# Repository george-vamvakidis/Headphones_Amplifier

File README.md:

# Headphones_Amplifier
Headphone amplifier design using NE5532 op-amp and Baxandall volume control. No pcb layout yet.

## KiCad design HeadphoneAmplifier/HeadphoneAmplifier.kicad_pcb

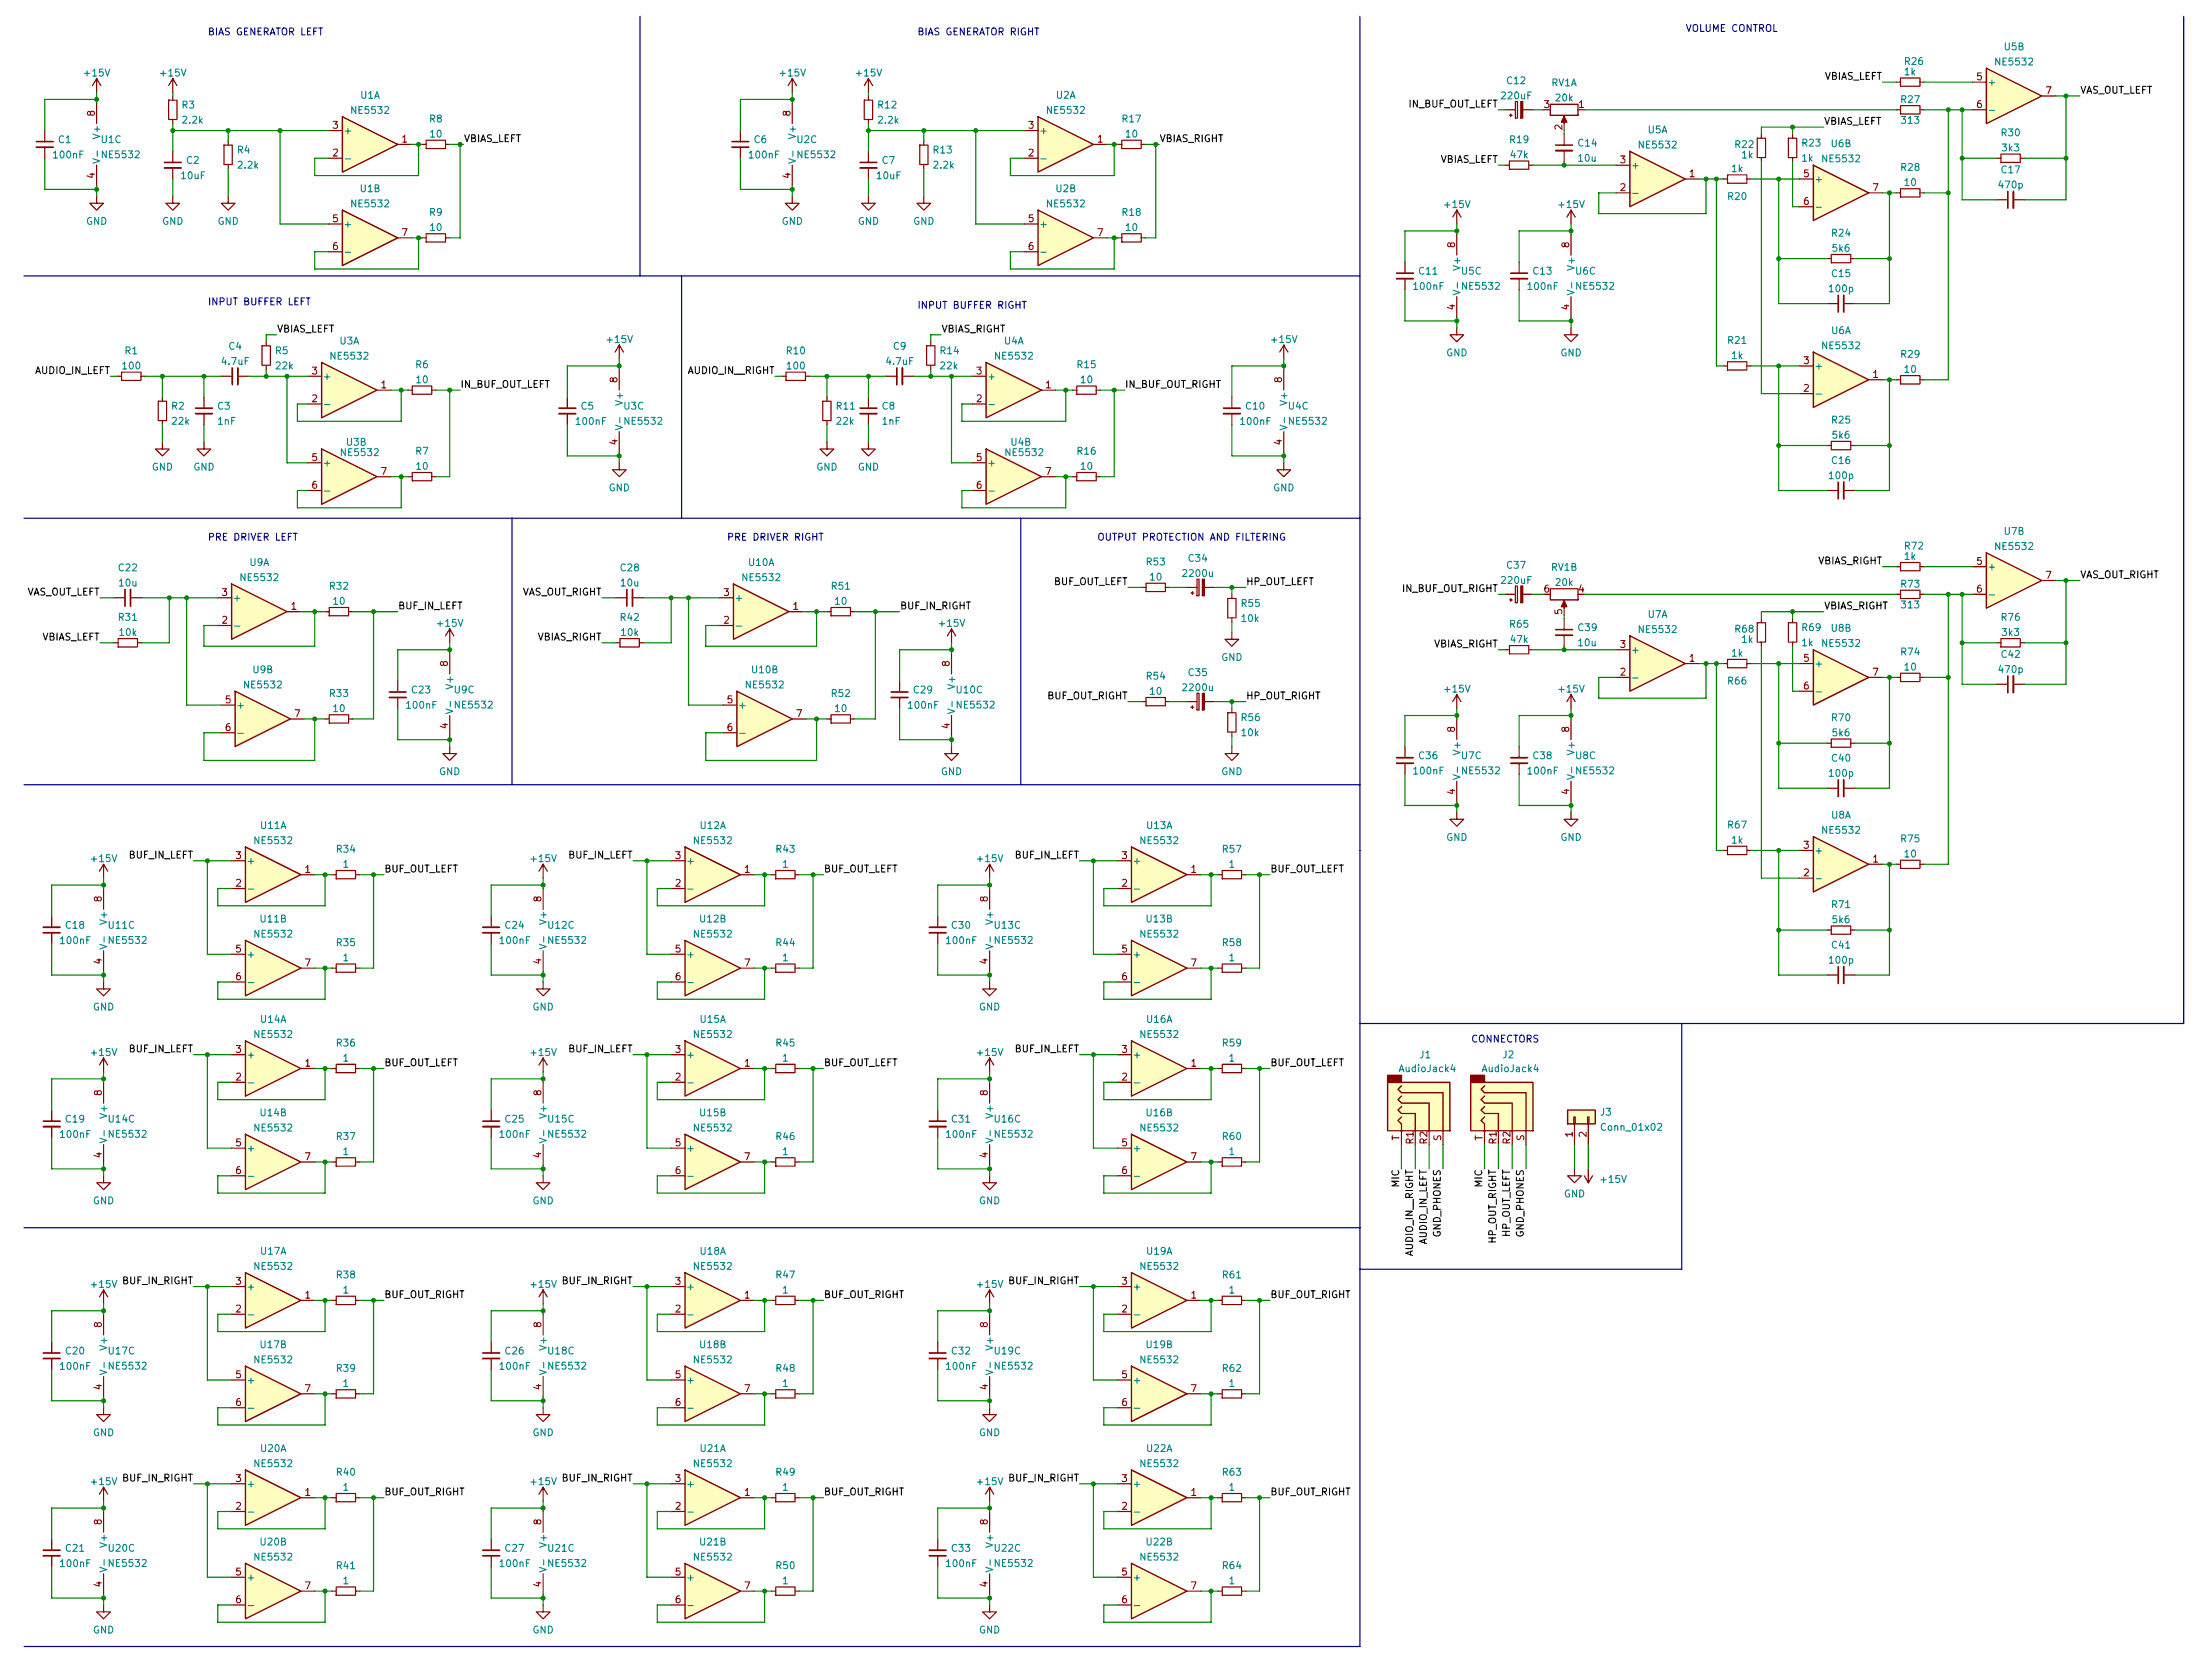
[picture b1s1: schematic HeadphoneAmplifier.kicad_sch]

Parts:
C1, C5, C6, C10, C11, C13, C18, C19, C20, C21, C23, C24, C25, C26, C27, C29, C30, C31, C32, C33, C36, C38: 100nF; C_0603_1608Metric
C2, C7: 10uF; C_0603_1608Metric
C3, C8: 1nF; C_0603_1608Metric
C4, C9: 4.7uF; C_0603_1608Metric
C12: 220uF; CP_Elec_4x5.4
C14, C22, C28, C39: 10u; C_0603_1608Metric
C15, C16, C40, C41: 100p; C_0603_1608Metric
C17, C42: 470p; C_0603_1608Metric
C34, C35: 2200u; CP_Radial_D16.0mm_P7.50mm
C37: 220uF; CP_Elec_10x10
J1, J2: AudioJack4; Jack_3.5mm_PJ320E_Horizontal
J3: Conn_01x02; TerminalBlock_Altech_AK300-2_P5.00mm
R1, R10: 100; R_1210_3225Metric
R2, R5, R11, R14: 22k; R_1210_3225Metric
R3, R4, R12, R13: 2.2k; R_1210_3225Metric
R6, R7, R8, R9, R15, R16, R17, R18, R28, R29, R32, R33, R51, R52, R53, R54, R74, R75: 10; R_1210_3225Metric
R19, R65: 47k; R_1210_3225Metric
R20, R21, R22, R23, R26, R66, R67, R68, R69, R72: 1k; R_1210_3225Metric
R24, R25, R70, R71: 5k6; R_1210_3225Metric
R27, R73: 313; R_1210_3225Metric
R30, R76: 3k3; R_1210_3225Metric
R31, R42, R55, R56: 10k; R_1210_3225Metric
R34, R35, R36, R37, R38, R39, R40, R41, R43, R44, R45, R46, R47, R48, R49, R50, R57, R58, R59, R60, R61, R62, R63, R64: 1; R_1210_3225Metric
RV1: 20k; Potentiometer_Piher_PC-16_Dual_Horizontal
U1, U2, U3, U4, U5, U6, U7, U8, U9, U10, U11, U12, U13, U14, U15, U16, U17, U18, U19, U20, U21, U22: NE5532; SOIC-8-1EP_3.9x4.9mm_P1.27mm_EP2.41x3.3mm

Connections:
+15V: C1.1, C5.1, C6.1, C10.1, C11.1, C13.1, C18.1, C19.1, C20.1, C21.1, C23.1, C24.1, C25.1, C26.1, C27.1, C29.1, C30.1, C31.1, C32.1, C33.1, C36.1, C38.1, J3.2, R3.1, R12.1, U1.8 (V+), U2.8 (V+), U3.8 (V+), U4.8 (V+), U5.8 (V+), U6.8 (V+), U7.8 (V+), U8.8 (V+), U9.8 (V+), U10.8 (V+), U11.8 (V+), U12.8 (V+), U13.8 (V+), U14.8 (V+), U15.8 (V+), U16.8 (V+), U17.8 (V+), U18.8 (V+), U19.8 (V+), U20.8 (V+), U21.8 (V+), U22.8 (V+)
/AUDIO_IN_LEFT: J1.R2, R1.1
/AUDIO_IN__RIGHT: J1.R1, R10.1
/BUF_IN_LEFT: R32.2, R33.2, U11.3 (+), U11.5 (+), U12.3 (+), U12.5 (+), U13.3 (+), U13.5 (+), U14.3 (+), U14.5 (+), U15.3 (+), U15.5 (+), U16.3 (+), U16.5 (+)
/BUF_IN_RIGHT: R51.2, R52.2, U17.3 (+), U17.5 (+), U18.3 (+), U18.5 (+), U19.3 (+), U19.5 (+), U20.3 (+), U20.5 (+), U21.3 (+), U21.5 (+), U22.3 (+), U22.5 (+)
/BUF_OUT_LEFT: R34.2, R35.2, R36.2, R37.2, R43.2, R44.2, R45.2, R46.2, R53.1, R57.2, R58.2, R59.2, R60.2
/BUF_OUT_RIGHT: R38.2, R39.2, R40.2, R41.2, R47.2, R48.2, R49.2, R50.2, R54.1, R61.2, R62.2, R63.2, R64.2
/GND_PHONES: J1.S, J2.S
/HP_OUT_LEFT: C34.2, J2.R2, R55.1
/HP_OUT_RIGHT: C35.2, J2.R1, R56.1
/IN_BUF_OUT_LEFT: C12.1, R6.2, R7.2
/IN_BUF_OUT_RIGHT: C37.1, R15.2, R16.2
/MIC: J1.T, J2.T
/VAS_OUT_LEFT: C17.2, C22.1, R30.2, U5.7
/VAS_OUT_RIGHT: C28.1, C42.2, R76.2, U7.7
/VBIAS_LEFT: R5.1, R8.2, R9.2, R19.1, R22.1, R23.1, R26.1, R31.1
/VBIAS_RIGHT: R14.1, R17.2, R18.2, R42.1, R65.1, R68.1, R69.1, R72.1
GND: C1.2, C2.2, C3.2, C5.2, C6.2, C7.2, C8.2, C10.2, C11.2, C13.2, C18.2, C19.2, C20.2, C21.2, C23.2, C24.2, C25.2, C26.2, C27.2, C29.2, C30.2, C31.2, C32.2, C33.2, C36.2, C38.2, J3.1, R2.2, R4.2, R11.2, R13.2, R55.2, R56.2, U1.4 (V-), U2.4 (V-), U3.4 (V-), U4.4 (V-), U5.4 (V-), U6.4 (V-), U7.4 (V-), U8.4 (V-), U9.4 (V-), U10.4 (V-), U11.4 (V-), U12.4 (V-), U13.4 (V-), U14.4 (V-), U15.4 (V-), U16.4 (V-), U17.4 (V-), U18.4 (V-), U19.4 (V-), U20.4 (V-), U21.4 (V-), U22.4 (V-)
unnamed: C2.1, R3.2, R4.1, U1.3 (+), U1.5 (+)
unnamed: C3.1, C4.1, R1.2, R2.1
unnamed: C4.2, R5.2, U3.3 (+), U3.5 (+)
unnamed: C7.1, R12.2, R13.1, U2.3 (+), U2.5 (+)
unnamed: C8.1, C9.1, R10.2, R11.1
unnamed: C9.2, R14.2, U4.3 (+), U4.5 (+)
unnamed: C12.2, RV1.3
unnamed: C14.1, RV1.2
unnamed: C14.2, R19.2, U5.3 (+)
unnamed: C15.1, R20.2, R24.1, U6.5 (+)
unnamed: C15.2, R24.2, R28.1, U6.7
unnamed: C16.1, R21.2, R25.1, U6.3 (+)
unnamed: C16.2, R25.2, R29.1, U6.1
unnamed: C17.1, R27.2, R28.2, R29.2, R30.1, U5.6 (-)
unnamed: C22.2, R31.2, U9.3 (+), U9.5 (+)
unnamed: C28.2, R42.2, U10.3 (+), U10.5 (+)
unnamed: C34.1, R53.2
unnamed: C35.1, R54.2
unnamed: C37.2, RV1.6
unnamed: C39.1, RV1.5
unnamed: C39.2, R65.2, U7.3 (+)
unnamed: C40.1, R66.2, R70.1, U8.5 (+)
unnamed: C40.2, R70.2, R74.1, U8.7
unnamed: C41.1, R67.2, R71.1, U8.3 (+)
unnamed: C41.2, R71.2, R75.1, U8.1
unnamed: C42.1, R73.2, R74.2, R75.2, R76.1, U7.6 (-)
unnamed: R6.1, U3.1, U3.2 (-)
unnamed: R7.1, U3.6 (-), U3.7
unnamed: R8.1, U1.1, U1.2 (-)
unnamed: R9.1, U1.6 (-), U1.7
unnamed: R15.1, U4.1, U4.2 (-)
unnamed: R16.1, U4.6 (-), U4.7
unnamed: R17.1, U2.1, U2.2 (-)
unnamed: R18.1, U2.6 (-), U2.7
unnamed: R20.1, R21.1, U5.1, U5.2 (-)
unnamed: R22.2, U6.2 (-)
unnamed: R23.2, U6.6 (-)
unnamed: R26.2, U5.5 (+)
unnamed: R27.1, RV1.1
unnamed: R32.1, U9.1, U9.2 (-)
unnamed: R33.1, U9.6 (-), U9.7
unnamed: R34.1, U11.1, U11.2 (-)
unnamed: R35.1, U11.6 (-), U11.7
unnamed: R36.1, U14.1, U14.2 (-)
unnamed: R37.1, U14.6 (-), U14.7
unnamed: R38.1, U17.1, U17.2 (-)
unnamed: R39.1, U17.6 (-), U17.7
unnamed: R40.1, U20.1, U20.2 (-)
unnamed: R41.1, U20.6 (-), U20.7
unnamed: R43.1, U12.1, U12.2 (-)
unnamed: R44.1, U12.6 (-), U12.7
unnamed: R45.1, U15.1, U15.2 (-)
unnamed: R46.1, U15.6 (-), U15.7
unnamed: R47.1, U18.1, U18.2 (-)
unnamed: R48.1, U18.6 (-), U18.7
unnamed: R49.1, U21.1, U21.2 (-)
unnamed: R50.1, U21.6 (-), U21.7
unnamed: R51.1, U10.1, U10.2 (-)
unnamed: R52.1, U10.6 (-), U10.7
unnamed: R57.1, U13.1, U13.2 (-)
unnamed: R58.1, U13.6 (-), U13.7
unnamed: R59.1, U16.1, U16.2 (-)
unnamed: R60.1, U16.6 (-), U16.7
unnamed: R61.1, U19.1, U19.2 (-)
unnamed: R62.1, U19.6 (-), U19.7
unnamed: R63.1, U22.1, U22.2 (-)
unnamed: R64.1, U22.6 (-), U22.7
unnamed: R66.1, R67.1, U7.1, U7.2 (-)
unnamed: R68.2, U8.2 (-)
unnamed: R69.2, U8.6 (-)
unnamed: R72.2, U7.5 (+)
unnamed: R73.1, RV1.4

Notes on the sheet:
PRE DRIVER RIGHT
PRE DRIVER LEFT
INPUT BUFFER LEFT
VOLUME CONTROL
OUTPUT PROTECTION AND FILTERING
CONNECTORS
INPUT BUFFER RIGHT
BIAS GENERATOR RIGHT
BIAS GENERATOR LEFT

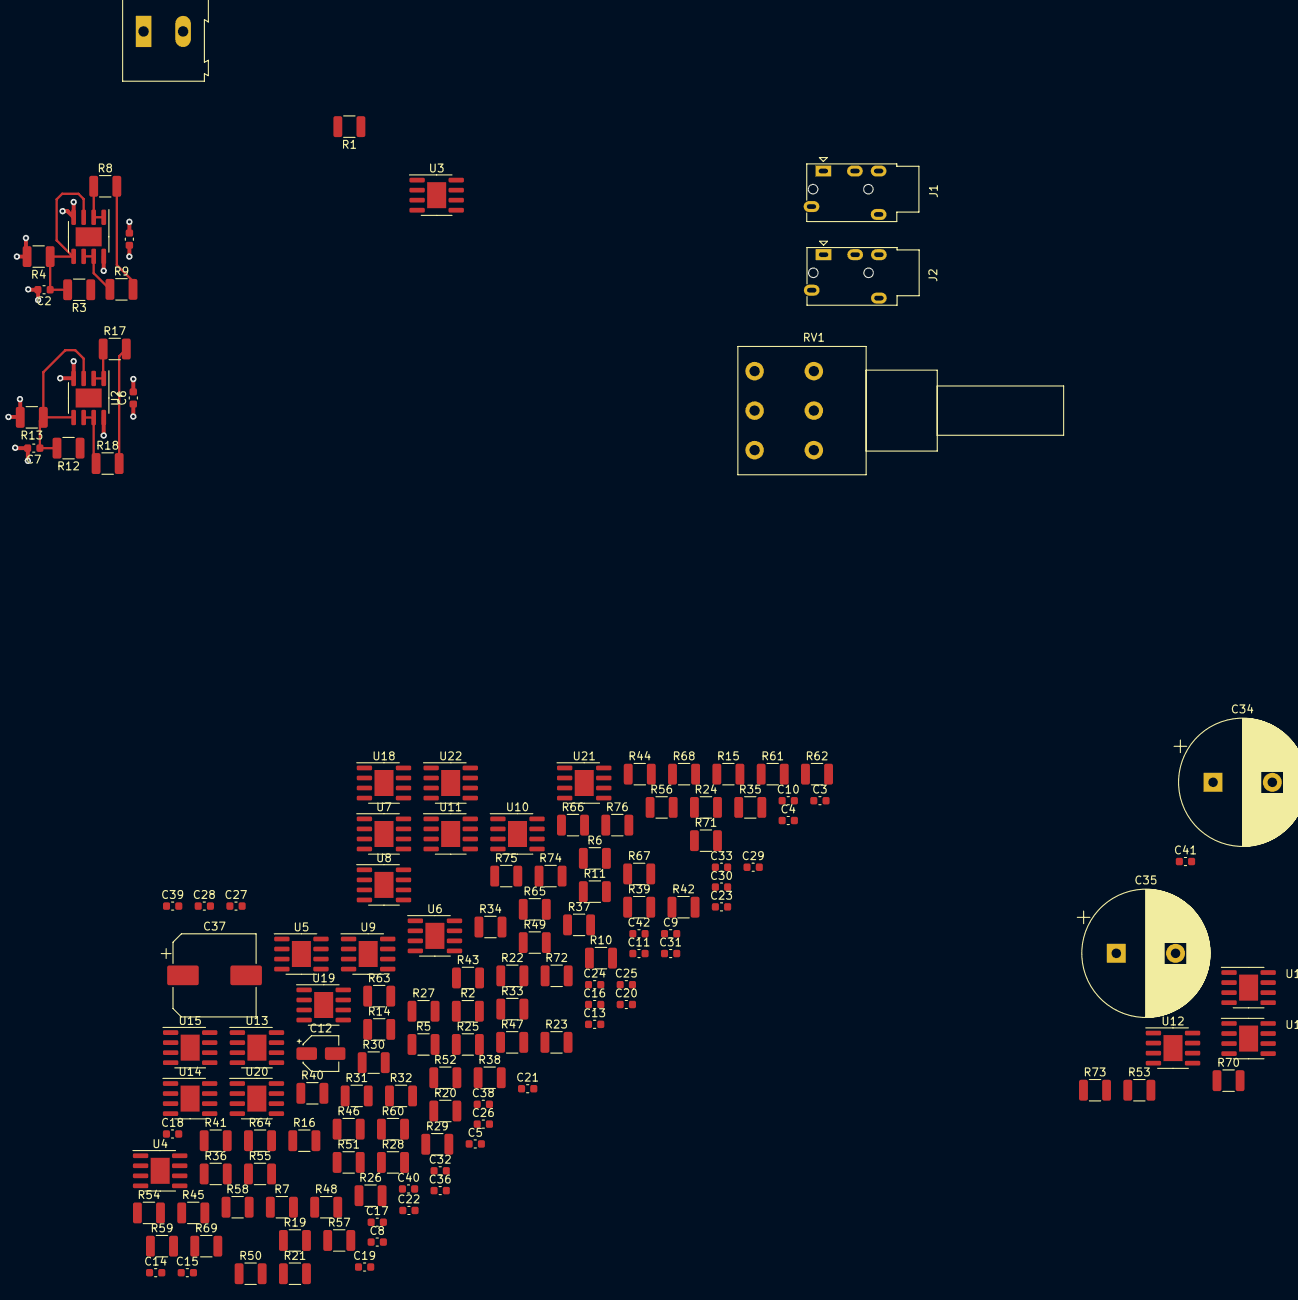
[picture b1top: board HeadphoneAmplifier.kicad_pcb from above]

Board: 2 copper layers, 144 parts (0 on the bottom side), 90 nets.
